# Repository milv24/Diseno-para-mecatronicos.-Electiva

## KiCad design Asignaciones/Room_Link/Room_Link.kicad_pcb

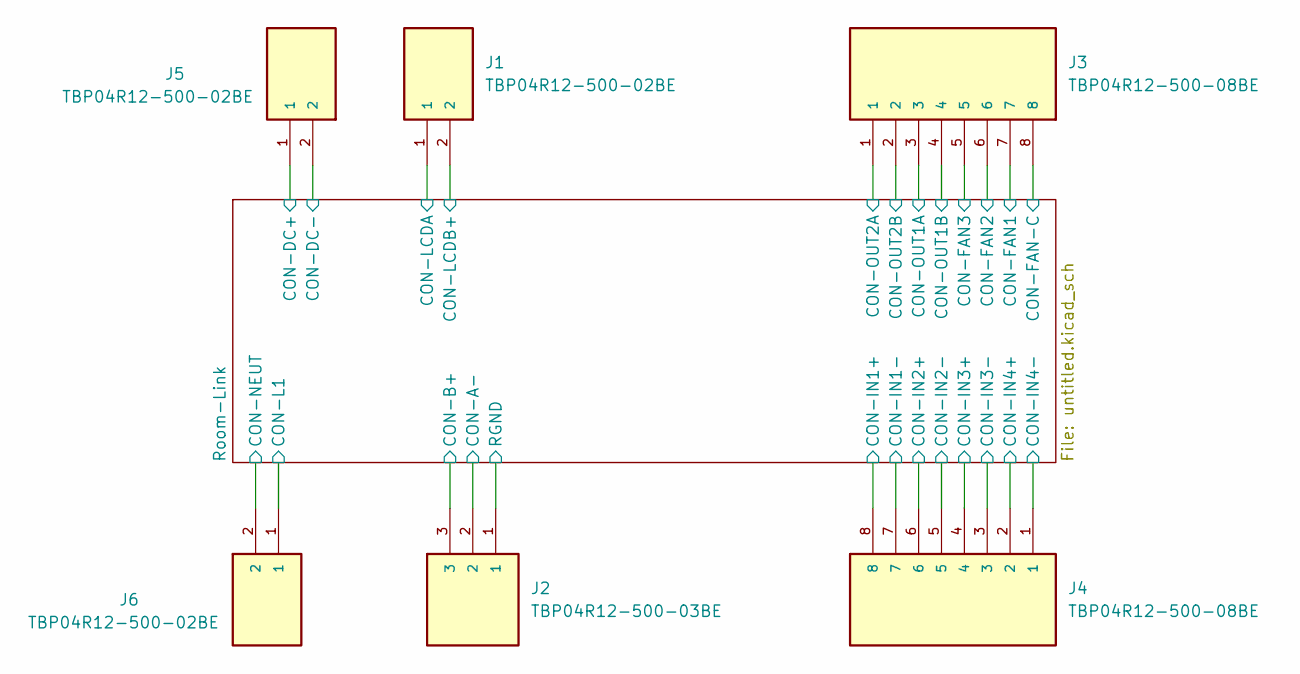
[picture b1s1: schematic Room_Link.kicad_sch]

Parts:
J1, J5, J6: TBP04R12-500-02BE; CUI_TBP04R12-500-02BE; PARTREV 1.0
J2: TBP04R12-500-03BE; CUI_TBP04R12-500-03BE; PARTREV 1.0
J3, J4: TBP04R12-500-08BE; CUI_TBP04R12-500-08BE; PARTREV 1.0

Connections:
/Room-Link/CON-A-: J2.2; also elsewhere on the board
/Room-Link/CON-DC+: J5.1
/Room-Link/CON-FAN1: J3.7; also elsewhere on the board
/Room-Link/CON-FAN2: J3.6; also elsewhere on the board
/Room-Link/CON-FAN3: J3.5; also elsewhere on the board
/Room-Link/CON-FAN-C: J3.8; also elsewhere on the board
/Room-Link/CON-IN1+: J4.8; also elsewhere on the board
/Room-Link/CON-IN1-: J4.7; also elsewhere on the board
/Room-Link/CON-IN2+: J4.6; also elsewhere on the board
/Room-Link/CON-IN2-: J4.5; also elsewhere on the board
/Room-Link/CON-IN3+: J4.4; also elsewhere on the board
/Room-Link/CON-IN3-: J4.3; also elsewhere on the board
/Room-Link/CON-IN4+: J4.2; also elsewhere on the board
/Room-Link/CON-IN4-: J4.1; also elsewhere on the board
/Room-Link/CON-L1: J6.1; also elsewhere on the board
/Room-Link/CON-LCDA: J1.1; also elsewhere on the board
/Room-Link/CON-LCDB+: J1.2; also elsewhere on the board
/Room-Link/CON-NEUT: J6.2; also elsewhere on the board
/Room-Link/CON-OUT1A: J3.3; also elsewhere on the board
/Room-Link/CON-OUT1B: J3.4; also elsewhere on the board
/Room-Link/CON-OUT2A: J3.2; also elsewhere on the board
/Room-Link/CON-OUT2B: J3.1; also elsewhere on the board
/Room-Link/RGND: J2.1; also elsewhere on the board

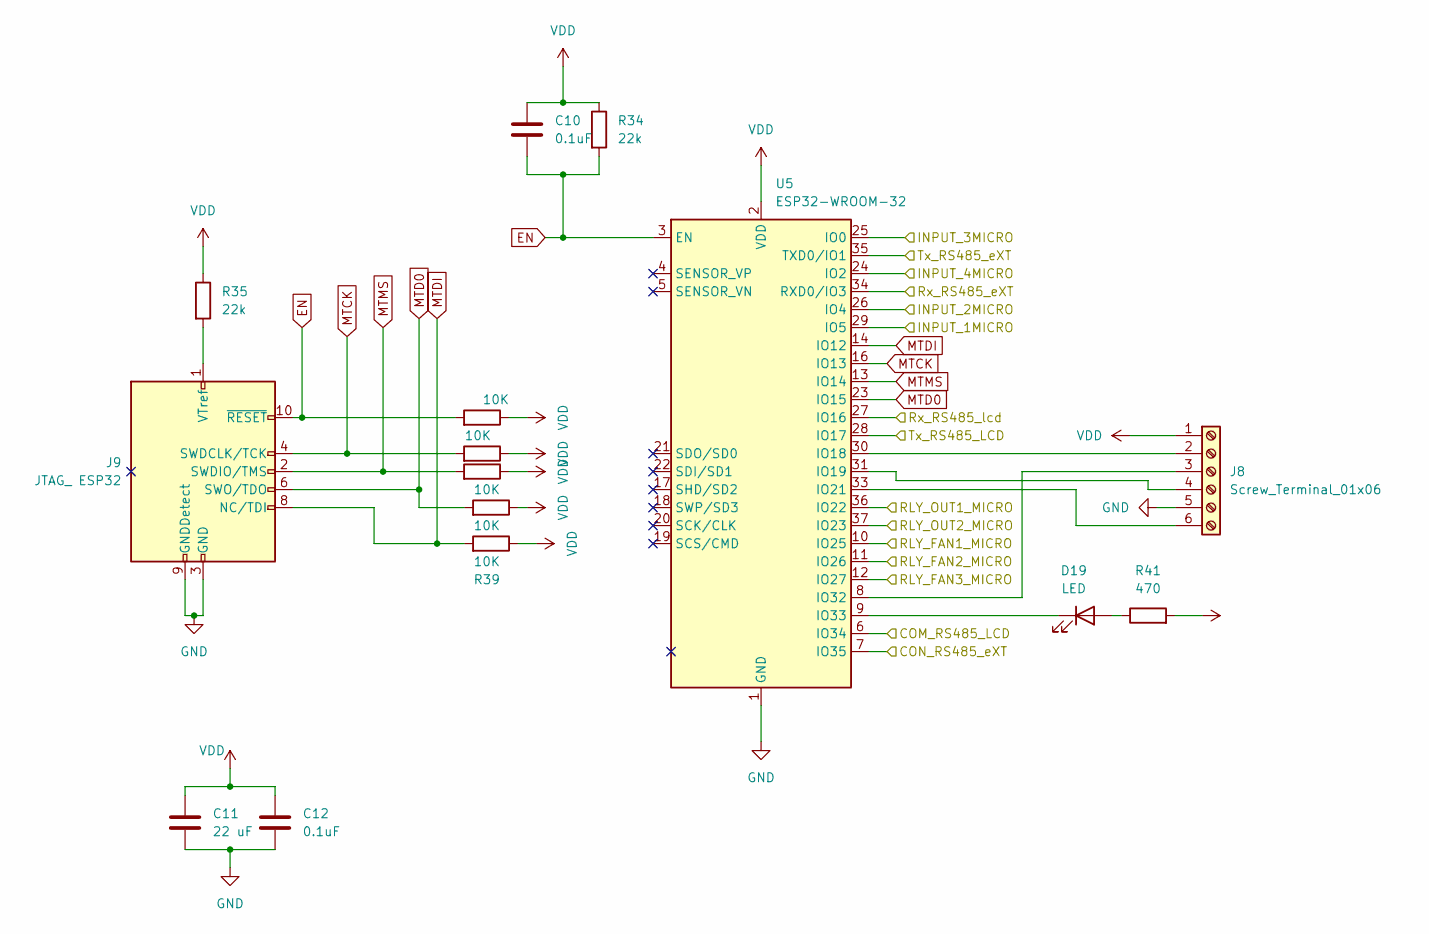
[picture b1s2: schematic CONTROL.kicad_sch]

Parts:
C10, C12: 0.1uF; C_0805_2012Metric
C11: 22 uF; C_0805_2012Metric
D19: LED; LED_0805_2012Metric
J8: Screw_Terminal_01x06; PinHeader_1x06_P2.54mm_Vertical_SMD_Pin1Left
J9: JTAG_ ESP32; PinHeader_2x05_P1.27mm_Vertical
R34, R35: 22k; R_0805_2012Metric
R36, R37, R38, R39, R40: 10K; R_0805_2012Metric
R41: 470; R_0805_2012Metric
U5: ESP32-WROOM-32

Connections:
/Room-Link/CONTROL/COM_RS485_LCD: U5.6 (IO34); also elsewhere on the board
/Room-Link/CONTROL/CON_RS485_eXT: U5.7 (IO35); also elsewhere on the board
/Room-Link/CONTROL/INPUT_1MICRO: U5.29 (IO5); also elsewhere on the board
/Room-Link/CONTROL/INPUT_2MICRO: U5.26 (IO4); also elsewhere on the board
/Room-Link/CONTROL/INPUT_3MICRO: U5.25 (IO0); also elsewhere on the board
/Room-Link/CONTROL/INPUT_4MICRO: U5.24 (IO2); also elsewhere on the board
/Room-Link/CONTROL/RLY_FAN1_MICRO: U5.10 (IO25); also elsewhere on the board
/Room-Link/CONTROL/RLY_FAN2_MICRO: U5.11 (IO26); also elsewhere on the board
/Room-Link/CONTROL/RLY_FAN3_MICRO: U5.12 (IO27); also elsewhere on the board
/Room-Link/CONTROL/RLY_OUT1_MICRO: U5.36 (IO22); also elsewhere on the board
/Room-Link/CONTROL/RLY_OUT2_MICRO: U5.37 (IO23); also elsewhere on the board
/Room-Link/CONTROL/Rx_RS485_eXT: U5.34 (RXD0/IO3); also elsewhere on the board
/Room-Link/CONTROL/Rx_RS485_lcd: U5.27 (IO16); also elsewhere on the board
/Room-Link/CONTROL/Tx_RS485_LCD: U5.28 (IO17); also elsewhere on the board
/Room-Link/CONTROL/Tx_RS485_eXT: U5.35 (TXD0/IO1); also elsewhere on the board
EN: C10.2, J9.10 (~RESET), R34.2, R40.2, U5.3 (EN)
MTCK: J9.4 (SWDCLK/TCK), R37.2, U5.16 (IO13)
MTD0: J9.6 (SWO/TDO), R38.2, U5.23 (IO15)
MTDI: J9.8 (NC/TDI), R39.2, U5.14 (IO12)
MTMS: J9.2 (SWDIO/TMS), R36.2, U5.13 (IO14)
unnamed: D19.2 (A), R41.1
unnamed: D19.1 (K), U5.9 (IO33)
unnamed: J8.2, U5.30 (IO18)
unnamed: J8.3, U5.8 (IO32)
unnamed: J8.4, U5.31 (IO19)
unnamed: J8.6, U5.33 (IO21)
unnamed: J9.1 (VTref), R35.2
VDD: C10.1, C11.1, C12.1, J8.1, R34.1, R35.1, R36.1, R37.1, R38.1, R39.1, R40.1, R41.2, U5.2 (VDD); also elsewhere on the board

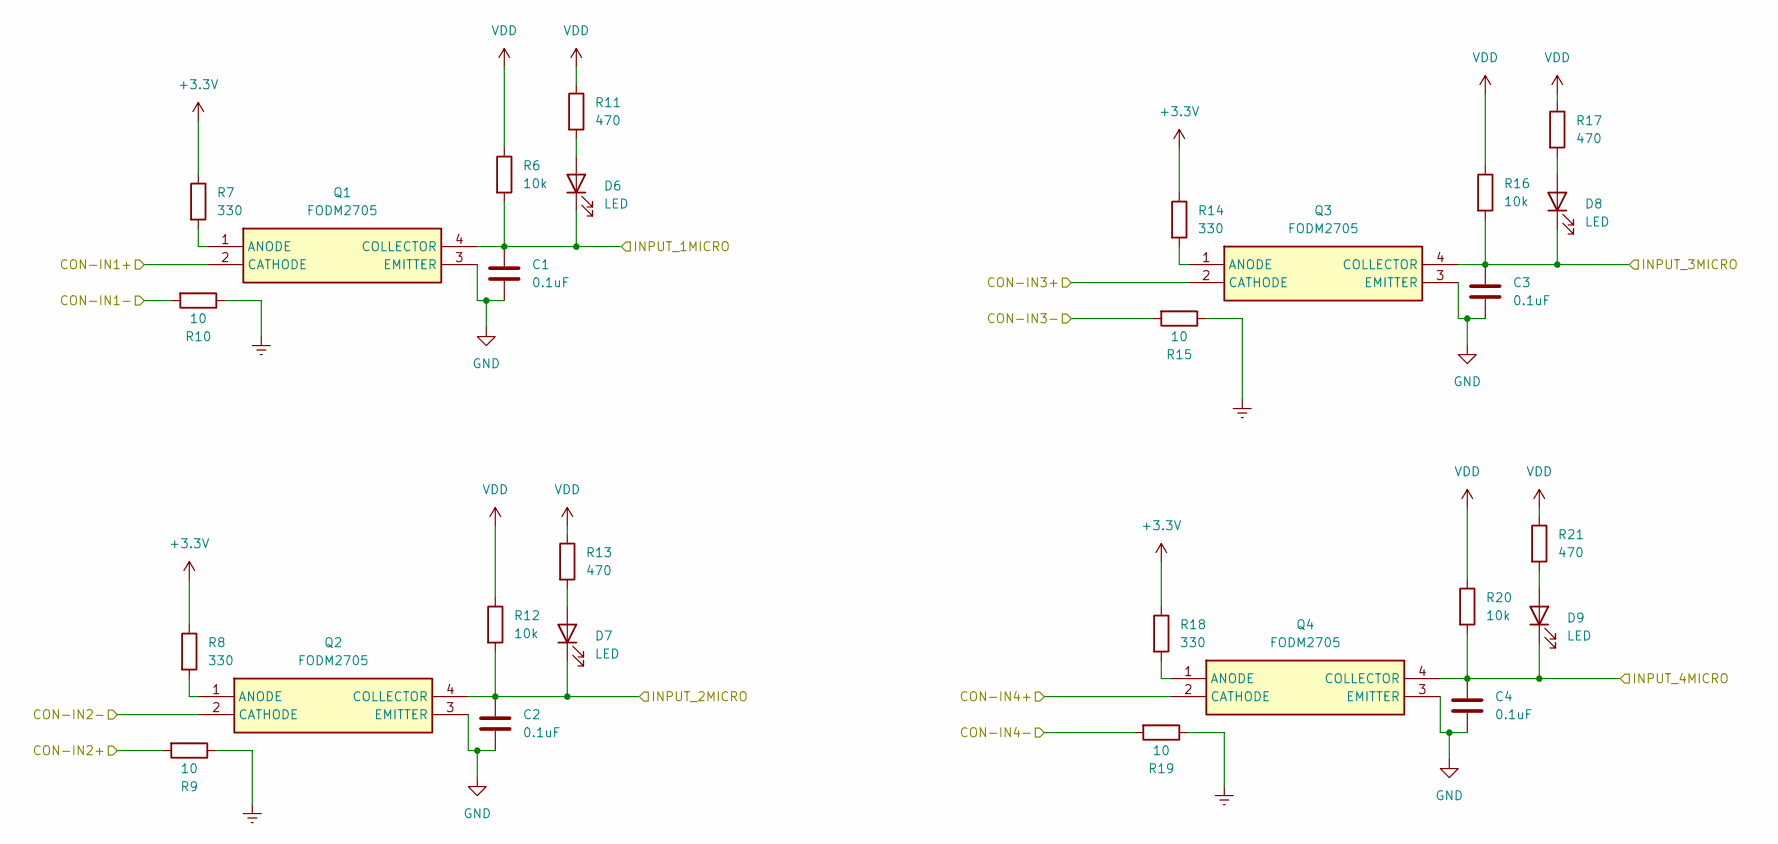
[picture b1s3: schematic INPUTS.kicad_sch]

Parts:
C1, C2, C3: 0.1uF; C_0805_2012Metric_Pad1.18x1.45mm_HandSolder
C4: 0.1uF; C_0805_2012Metric
D6, D7, D8, D9: LED; LED_0805_2012Metric
Q1, Q2, Q3, Q4: FODM2705; Manufacturer_Part_Number FODM2705; Mouser Part Number 512-FODM2705
R6, R12, R16, R20: 10k; R_0805_2012Metric
R7, R8, R14, R18: 330; R_0805_2012Metric
R9, R10, R15, R19: 10; R_0805_2012Metric
R11, R13, R17, R21: 470; R_0805_2012Metric

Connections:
+3.3V: R7.1, R8.1, R14.1, R18.1; also elsewhere on the board
/Room-Link/CON-IN1+: Q1.2 (CATHODE); also elsewhere on the board
/Room-Link/CON-IN1-: R10.2; also elsewhere on the board
/Room-Link/CON-IN2+: R9.2; also elsewhere on the board
/Room-Link/CON-IN2-: Q2.2 (CATHODE); also elsewhere on the board
/Room-Link/CON-IN3+: Q3.2 (CATHODE); also elsewhere on the board
/Room-Link/CON-IN3-: R15.2; also elsewhere on the board
/Room-Link/CON-IN4+: Q4.2 (CATHODE); also elsewhere on the board
/Room-Link/CON-IN4-: R19.2; also elsewhere on the board
/Room-Link/CONTROL/INPUT_1MICRO: C1.1, D6.1 (K), Q1.4 (COLLECTOR), R6.2; also elsewhere on the board
/Room-Link/CONTROL/INPUT_2MICRO: C2.1, D7.1 (K), Q2.4 (COLLECTOR), R12.2; also elsewhere on the board
/Room-Link/CONTROL/INPUT_3MICRO: C3.1, D8.1 (K), Q3.4 (COLLECTOR), R16.2; also elsewhere on the board
/Room-Link/CONTROL/INPUT_4MICRO: C4.1, D9.1 (K), Q4.4 (COLLECTOR), R20.2; also elsewhere on the board
Earth: R9.1, R10.1, R15.1, R19.1; also elsewhere on the board
unnamed: D6.2 (A), R11.2
unnamed: D7.2 (A), R13.2
unnamed: D8.2 (A), R17.2
unnamed: D9.2 (A), R21.2
unnamed: Q1.1 (ANODE), R7.2
unnamed: Q2.1 (ANODE), R8.2
unnamed: Q3.1 (ANODE), R14.2
unnamed: Q4.1 (ANODE), R18.2
VDD: R6.1, R11.1, R12.1, R13.1, R16.1, R17.1, R20.1, R21.1; also elsewhere on the board

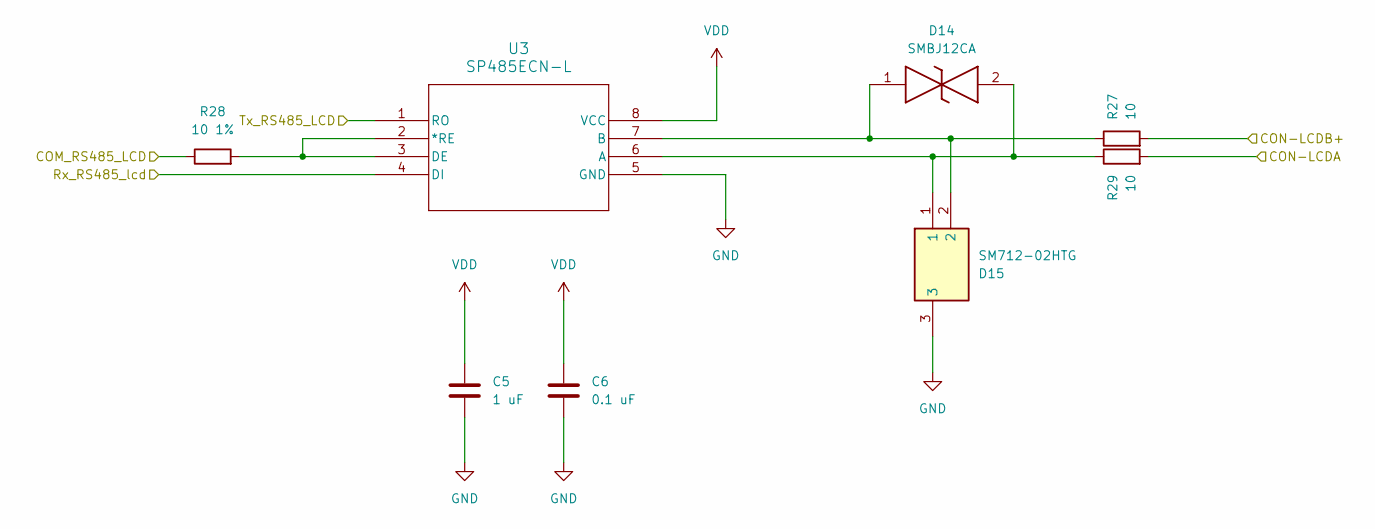
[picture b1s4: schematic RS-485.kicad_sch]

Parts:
C5: 1 uF; C_0805_2012Metric
C6: 0.1 uF; C_0805_2012Metric
D14: SMBJ12CA; Mouser Part Number 652-SMBJ12CA
D15: SM712-02HTG; SOT-23; Manufacturer_Part_Number SM712-02HTG; Mouser Part Number 576-SM712-02HTG
R27, R29: 10; R_0805_2012Metric
R28: 10 1%; R_0805_2012Metric
U3: SP485ECN-L; NSOIC-8-L

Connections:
/Room-Link/CON-LCDA: R29.2; also elsewhere on the board
/Room-Link/CON-LCDB+: R27.2; also elsewhere on the board
/Room-Link/CONTROL/COM_RS485_LCD: R28.1; also elsewhere on the board
/Room-Link/CONTROL/Rx_RS485_lcd: U3.4 (DI); also elsewhere on the board
/Room-Link/CONTROL/Tx_RS485_LCD: U3.1 (RO); also elsewhere on the board
unnamed: R28.2, U3.2 (*RE), U3.3 (DE)
unnamed: D14.2, D15.1, R29.1, U3.6 (A)
unnamed: D14.1, D15.2, R27.1, U3.7 (B)
VDD: C5.1, C6.1, U3.8 (VCC); also elsewhere on the board

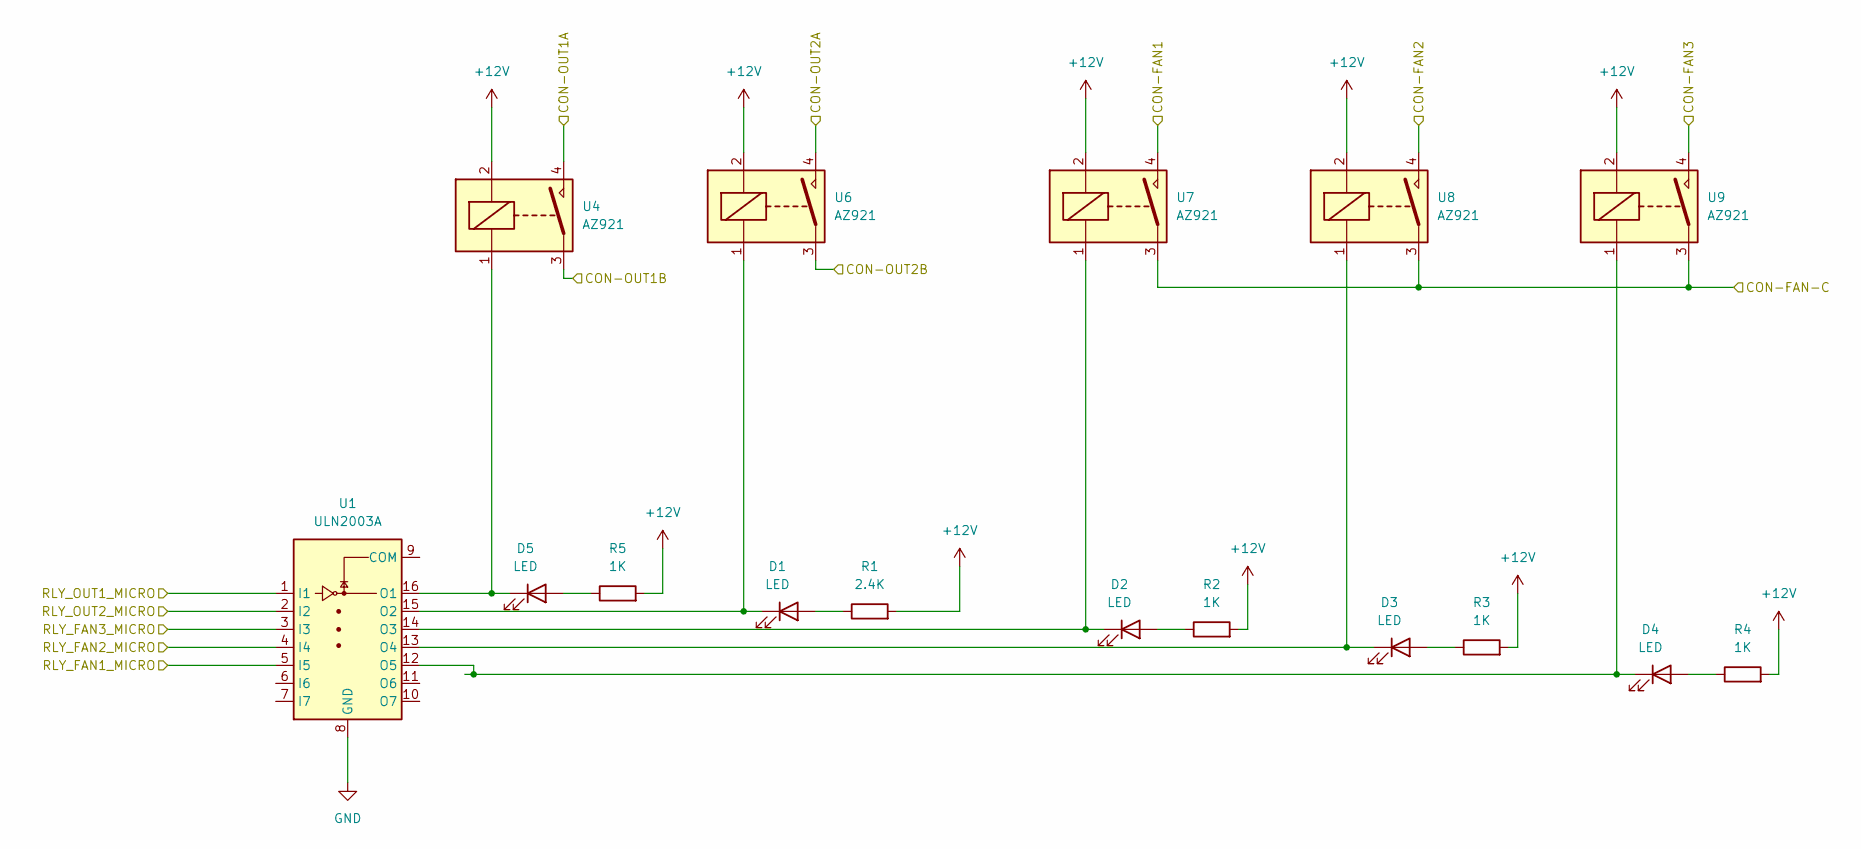
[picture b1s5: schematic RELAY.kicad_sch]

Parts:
D1, D2, D3, D4, D5: LED; LED_0805_2012Metric
R1: 2.4K; R_0805_2012Metric
R2, R3, R4, R5: 1K; R_0805_2012Metric
U1: ULN2003A; SOIC-16_3.9x9.9mm_P1.27mm
U4, U6, U7, U8, U9: AZ921

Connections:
/Room-Link/CON-FAN1: U7.4; also elsewhere on the board
/Room-Link/CON-FAN2: U8.4; also elsewhere on the board
/Room-Link/CON-FAN3: U9.4; also elsewhere on the board
/Room-Link/CON-FAN-C: U7.3, U8.3, U9.3; also elsewhere on the board
/Room-Link/CON-OUT1A: U4.4; also elsewhere on the board
/Room-Link/CON-OUT1B: U4.3; also elsewhere on the board
/Room-Link/CON-OUT2A: U6.4; also elsewhere on the board
/Room-Link/CON-OUT2B: U6.3; also elsewhere on the board
/Room-Link/CONTROL/RLY_FAN1_MICRO: U1.5 (I5); also elsewhere on the board
/Room-Link/CONTROL/RLY_FAN2_MICRO: U1.4 (I4); also elsewhere on the board
/Room-Link/CONTROL/RLY_FAN3_MICRO: U1.3 (I3); also elsewhere on the board
/Room-Link/CONTROL/RLY_OUT1_MICRO: U1.1 (I1); also elsewhere on the board
/Room-Link/CONTROL/RLY_OUT2_MICRO: U1.2 (I2); also elsewhere on the board
unnamed: D1.2 (A), R1.1
unnamed: D1.1 (K), U1.15 (O2), U6.1
unnamed: D2.2 (A), R2.1
unnamed: D2.1 (K), U1.14 (O3), U7.1
unnamed: D3.2 (A), R3.1
unnamed: D3.1 (K), U1.13 (O4), U8.1
unnamed: D4.2 (A), R4.1
unnamed: D4.1 (K), U1.12 (O5), U9.1
unnamed: D5.2 (A), R5.1
unnamed: D5.1 (K), U1.16 (O1), U4.1

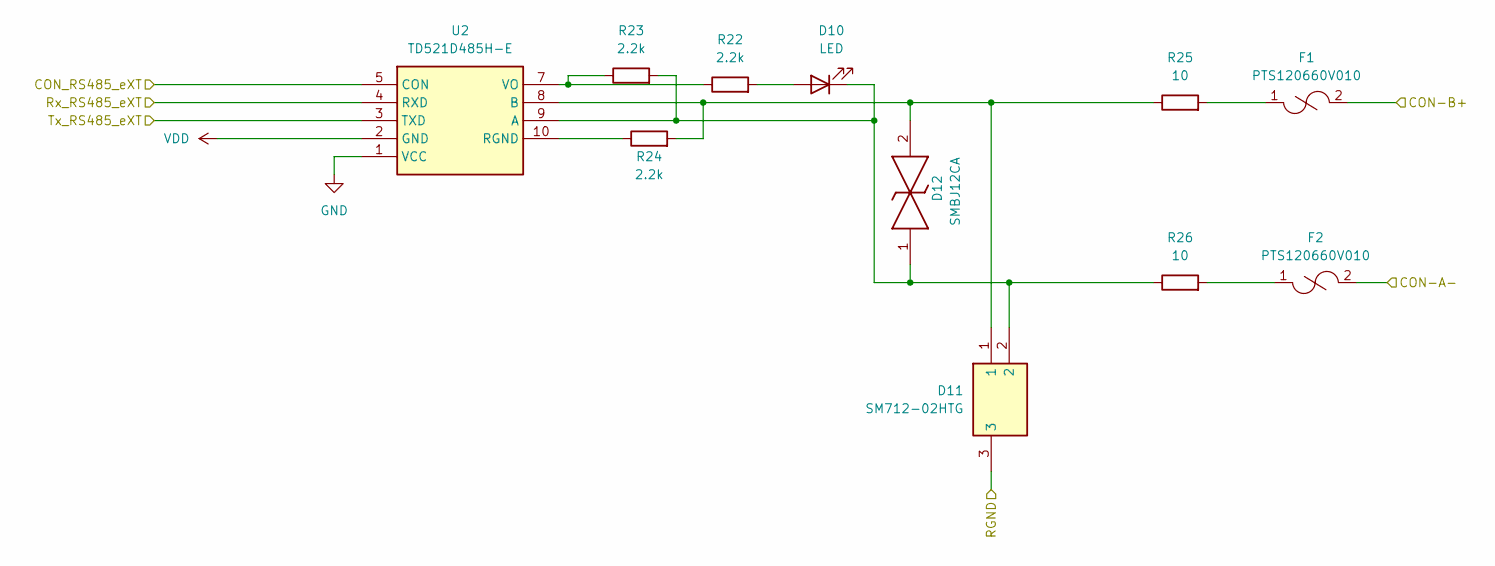
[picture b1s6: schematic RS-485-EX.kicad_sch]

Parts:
D10: LED; LED_0805_2012Metric
D11: SM712-02HTG; SOT-23; Manufacturer_Part_Number SM712-02HTG; Mouser Part Number 576-SM712-02HTG
D12: SMBJ12CA; Mouser Part Number 652-SMBJ12CA
F1, F2: PTS120660V010; FUSC3216X68N
R22, R23, R24: 2.2k; R_0805_2012Metric
R25, R26: 10; R_0805_2012Metric
U2: TD521D485H-E; Manufacturer_Part_Number TD521D485

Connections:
/Room-Link/CON-A-: F2.2; also elsewhere on the board
/Room-Link/CONTROL/CON_RS485_eXT: U2.5 (CON); also elsewhere on the board
/Room-Link/CONTROL/Rx_RS485_eXT: U2.4 (RXD); also elsewhere on the board
/Room-Link/CONTROL/Tx_RS485_eXT: U2.3 (TXD); also elsewhere on the board
/Room-Link/RGND: D11.3; also elsewhere on the board
unnamed: D10.2 (A), R22.2
unnamed: D10.1 (K), D11.2, D12.1, R23.2, R26.1, U2.9 (A)
unnamed: F1.1, R25.2
unnamed: F2.1, R26.2
unnamed: D11.1, D12.2, R24.2, R25.1, U2.8 (B)
unnamed: R24.1, U2.10 (RGND)
unnamed: R22.1, R23.1, U2.7 (VO)
VDD: U2.2 (GND); also elsewhere on the board

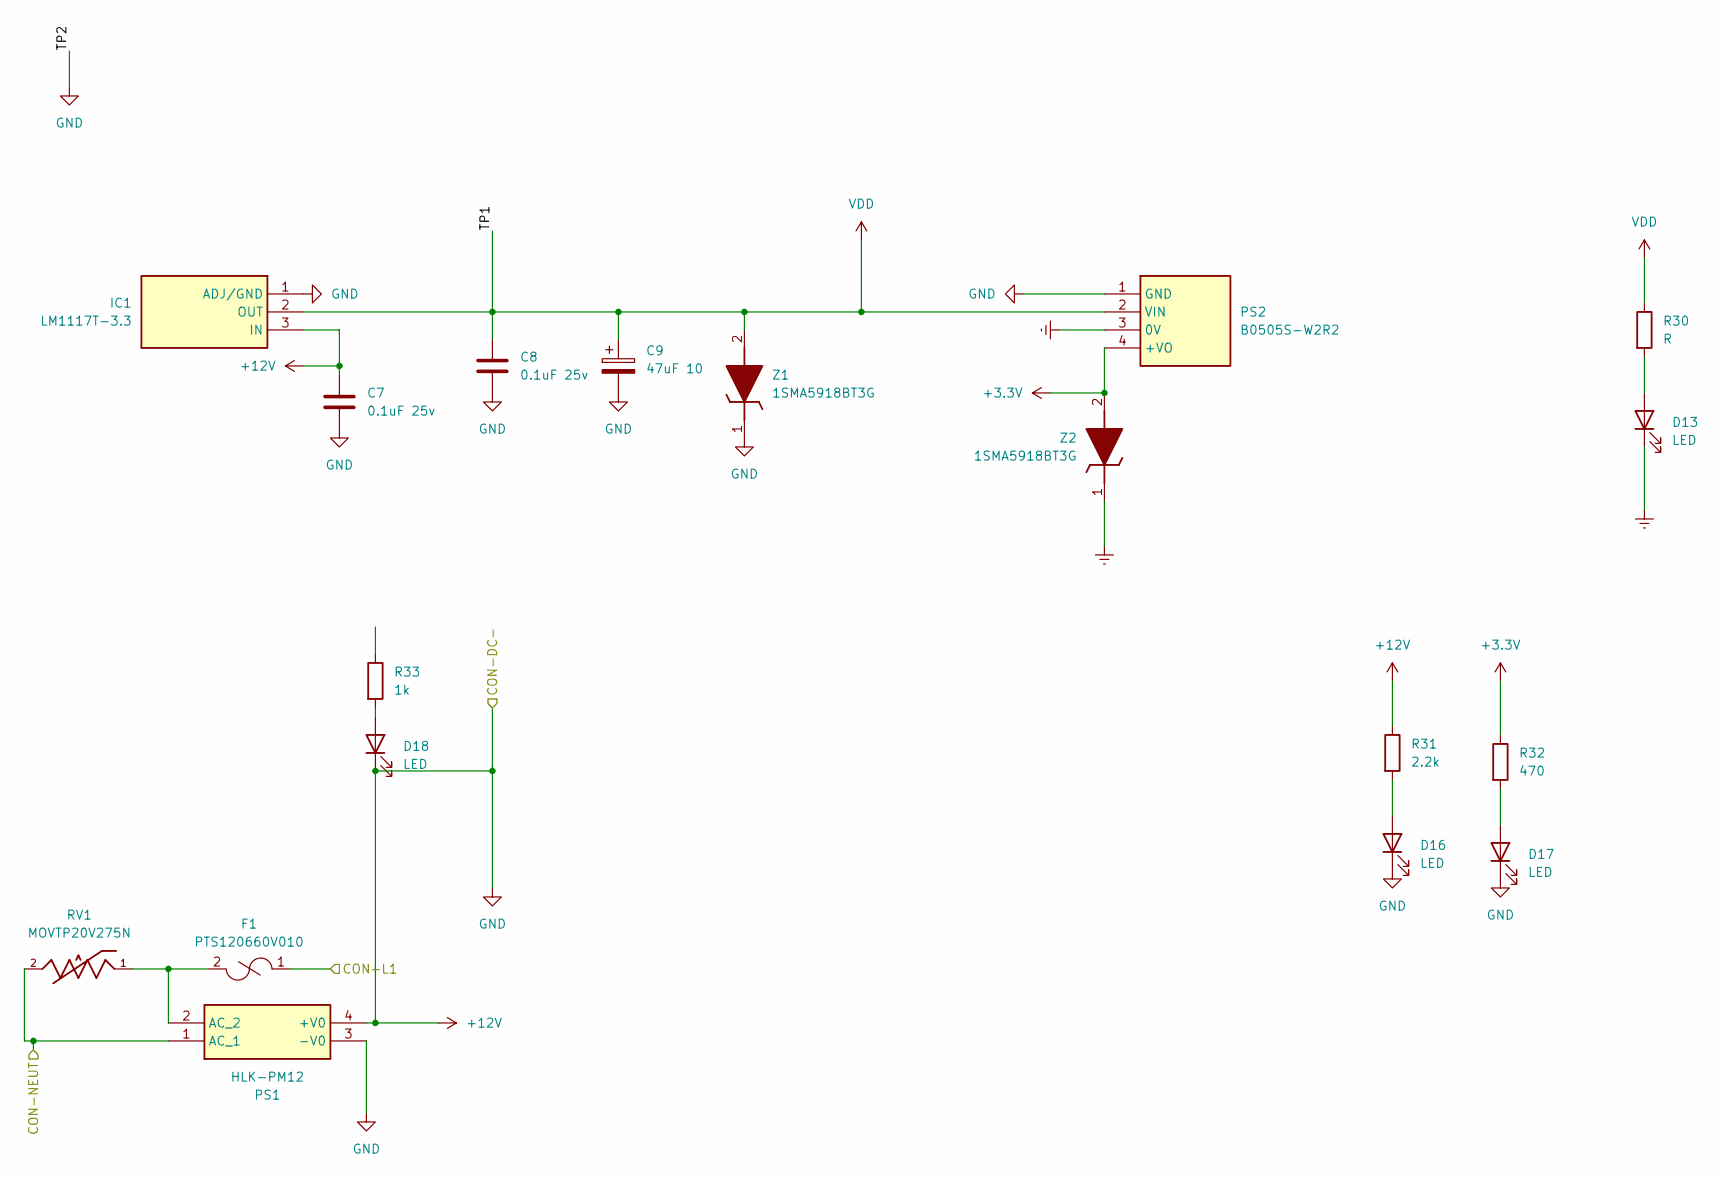
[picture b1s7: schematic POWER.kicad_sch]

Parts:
C7, C8: 0.1uF 25v; C_0805_2012Metric
C9: 47uF 10; C_0805_2012Metric
D13, D16, D17, D18: LED; LED_0805_2012Metric
F1: PTS120660V010; Fuseholder_Cylinder-5x20mm_Stelvio-Kontek_PTF78_Horizontal_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
IC1: LM1117T-3.3; TO254P470X1016X2222-3P; Manufacturer_Part_Number LM1117T-3.3; Mouser Part Number 926-LM1117T-33
PS1: HLK-PM12; HLKPM12; Manufacturer_Part_Number HLK-PM12
PS2: B0505S-W2R2; B0505SW2R2; Manufacturer_Part_Number B0505S-W2R2
R30: R; R_0805_2012Metric
R31: 2.2k; R_0805_2012Metric
R32: 470; R_0805_2012Metric
R33: 1k; R_0805_2012Metric
RV1: MOVTP20V275N; B72210S1140K501; Manufacturer_Part_Number MOVTP20V275N
Z1, Z2: 1SMA5918BT3G; D_SMB; Manufacturer_Part_Number 1SMA5918BT3G; Mouser Part Number 863-1SMA5918BT3G

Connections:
+3.3V: PS2.4 (+VO), R32.1, Z2.2 (A); also elsewhere on the board
/Room-Link/CON-NEUT: PS1.1 (AC_1), RV1.2; also elsewhere on the board
Earth: D13.1 (K), PS2.3 (0V), Z2.1 (K); also elsewhere on the board
unnamed: D13.2 (A), R30.2
unnamed: D16.2 (A), R31.2
unnamed: D17.2 (A), R32.2
unnamed: D18.2 (A), R33.2
unnamed 67: F1.1; also elsewhere on the board
VDD: C8.1, C9.1, IC1.2 (OUT), PS2.2 (VIN), R30.1, Z1.2 (A); also elsewhere on the board

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
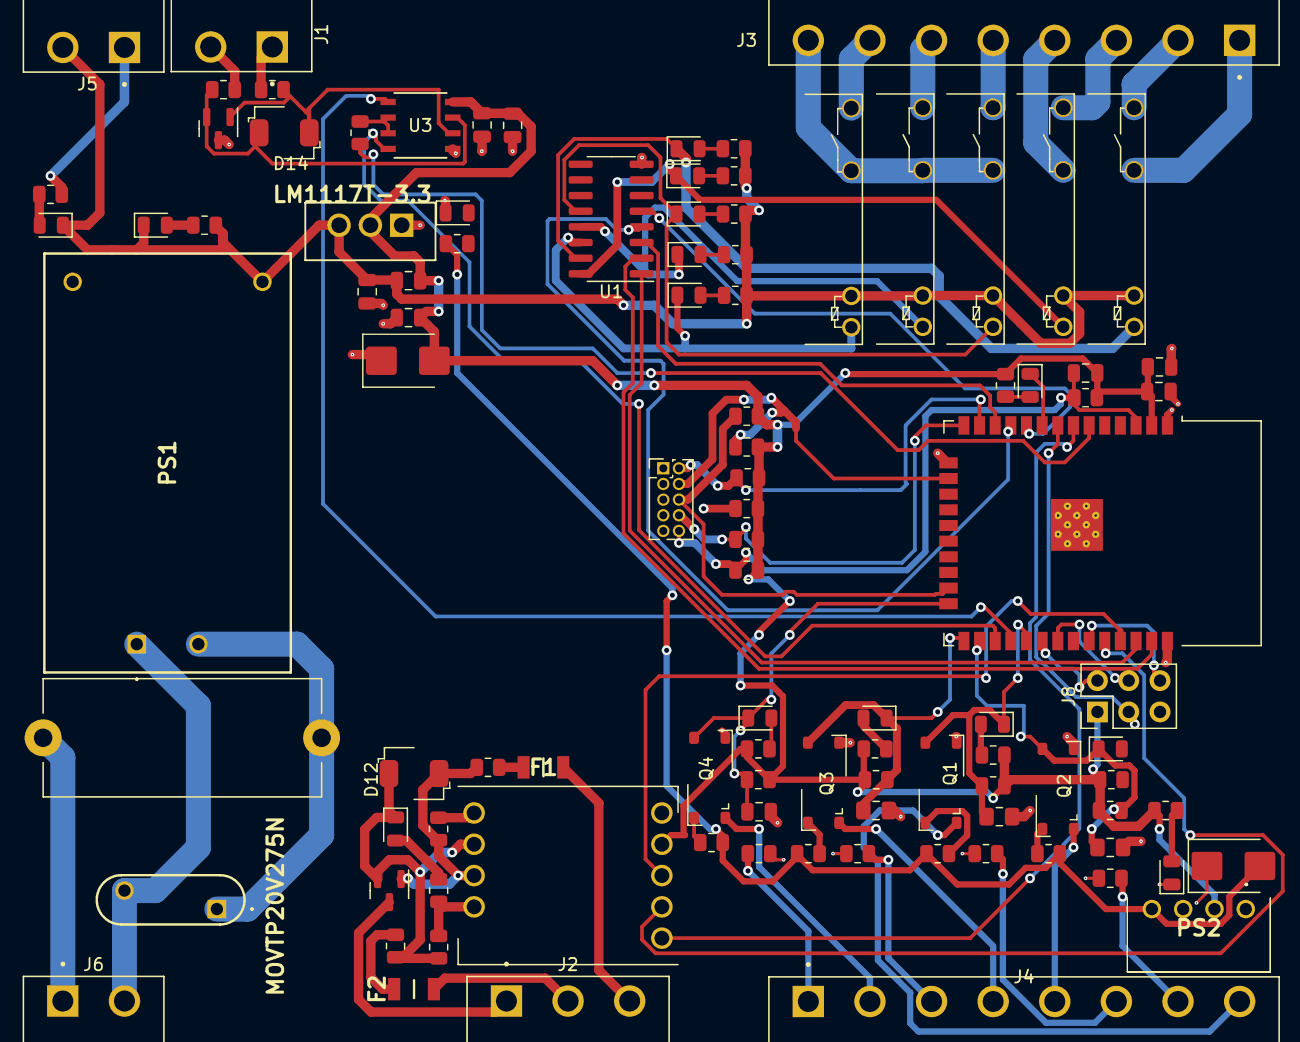
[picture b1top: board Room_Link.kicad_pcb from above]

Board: 4 copper layers, 102 parts (0 on the bottom side), 88 nets.

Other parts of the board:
F3: PTS120660V010; Fuseholder_Cylinder-5x20mm_Stelvio-Kontek_PTF78_Horizontal_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

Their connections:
/Room-Link/CON-L1: F3.1; also elsewhere on the board

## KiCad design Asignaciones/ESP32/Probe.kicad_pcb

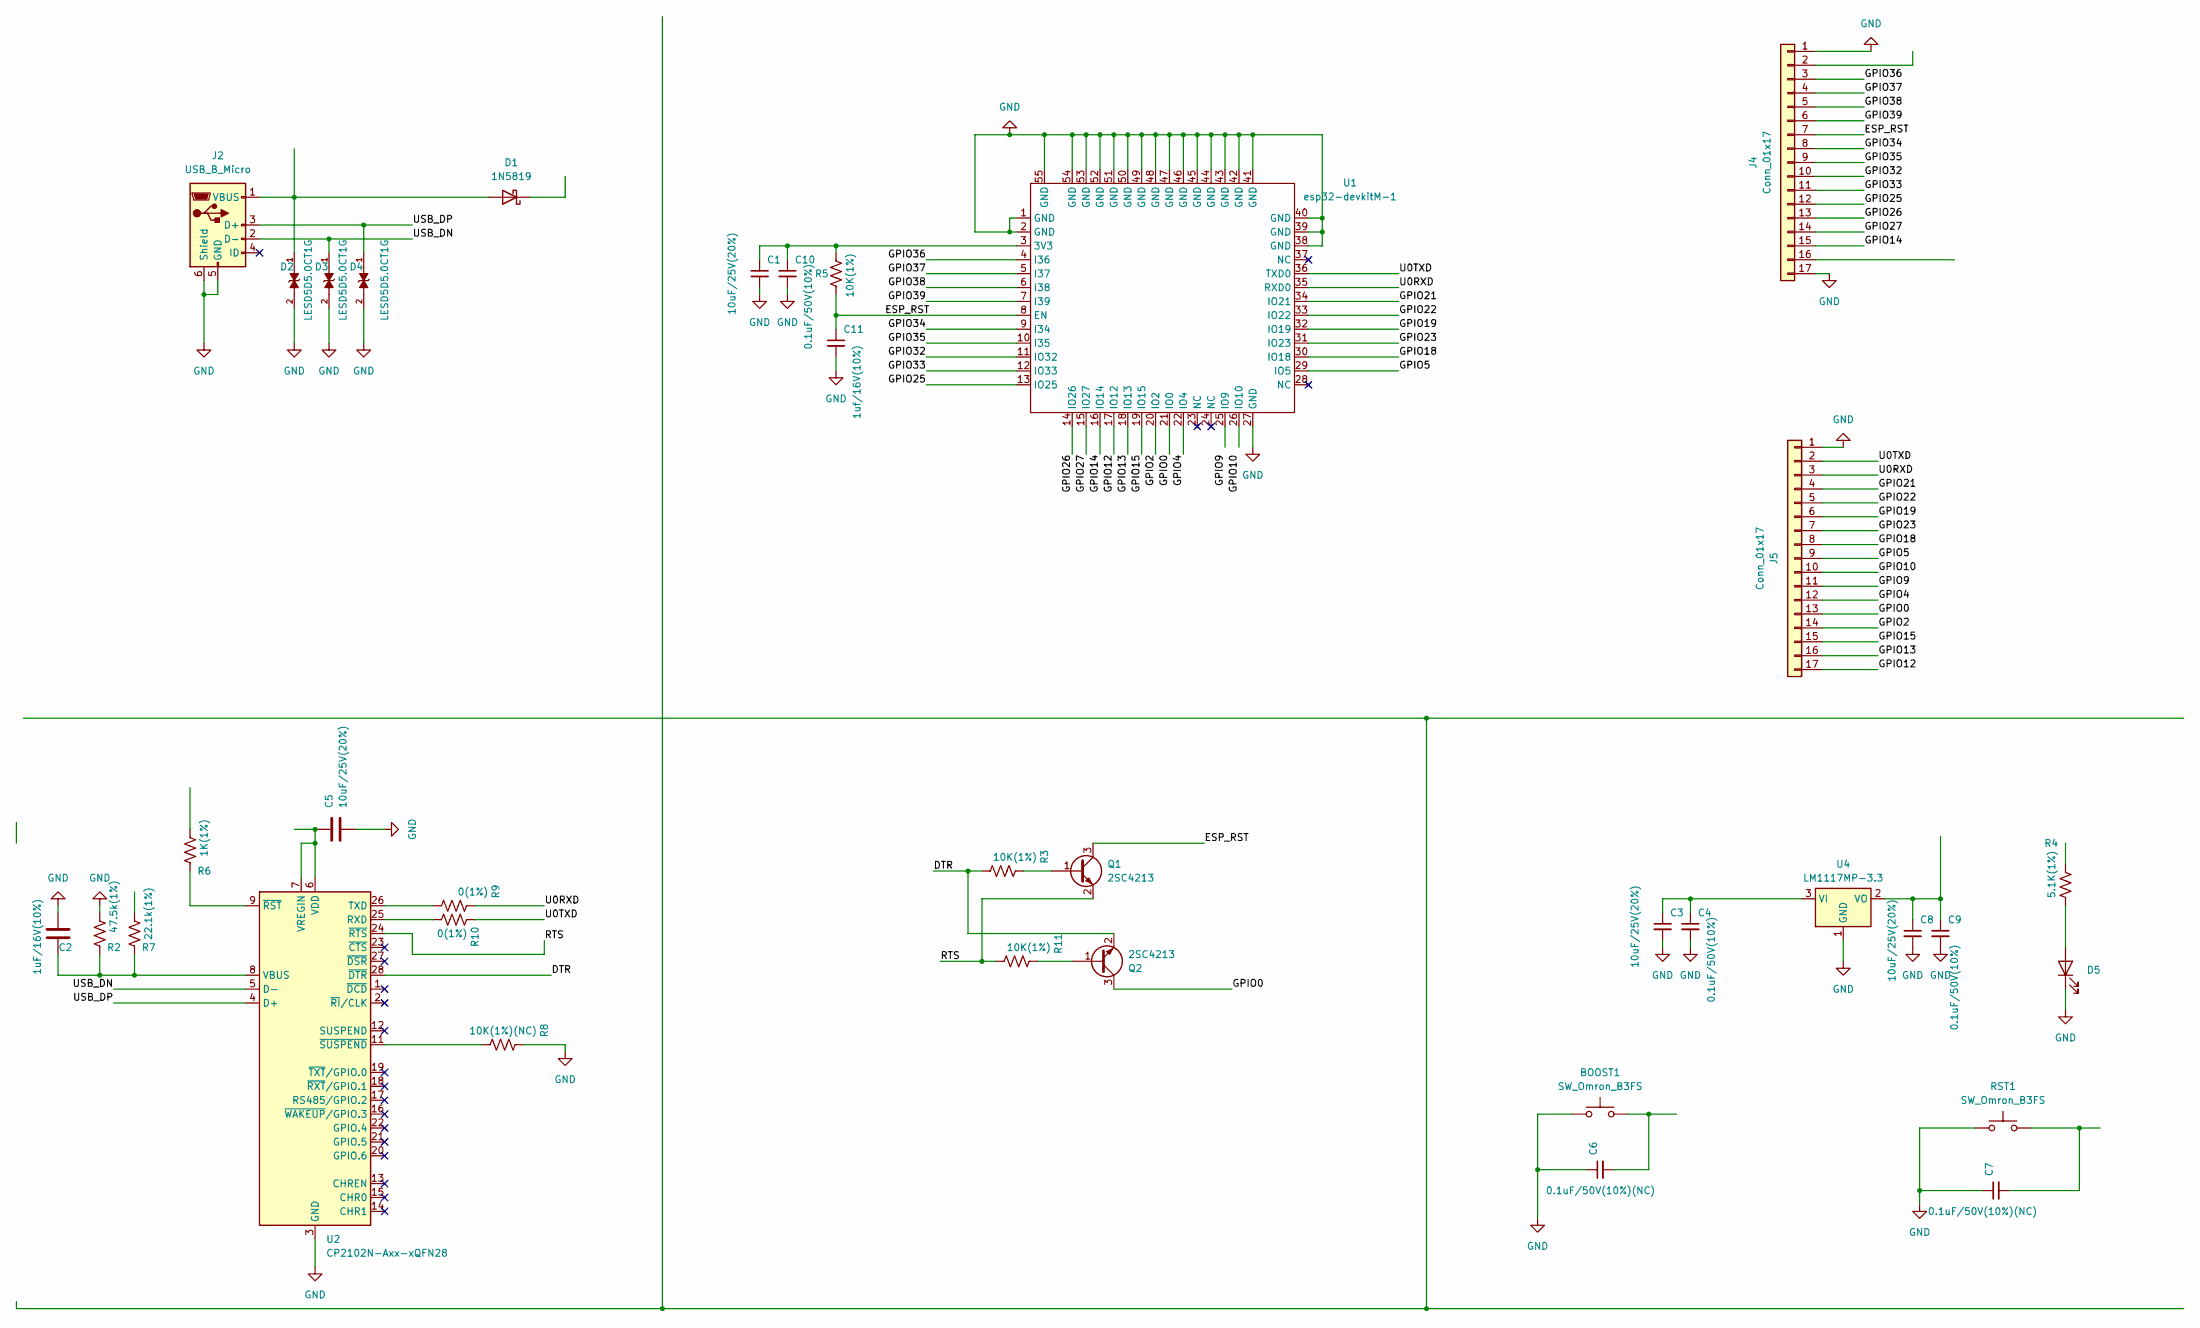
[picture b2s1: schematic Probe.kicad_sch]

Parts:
BOOST1: SW_Omron_B3FS; SW_SPST_PTS810
C1, C3, C5, C8: 10uF/25V(20%); C_0805_2012Metric_Pad1.18x1.45mm_HandSolder
C2: 1uF/16V(10%); C_0805_2012Metric_Pad1.18x1.45mm_HandSolder
C4, C9, C10: 0.1uF/50V(10%); C_0805_2012Metric_Pad1.18x1.45mm_HandSolder
C6, C7: 0.1uF/50V(10%)(NC); C_0805_2012Metric_Pad1.18x1.45mm_HandSolder
C11: 1uf/16V(10%); C_0805_2012Metric_Pad1.18x1.45mm_HandSolder
D1: 1N5819; D_0805_2012Metric_Pad1.15x1.40mm_HandSolder
D2, D3, D4: LESD5D5.0CT1G; TVS_LESD5D5.0CT1G; PARTREV O
D5: LED; LED_0805_2012Metric
J2: USB_B_Micro; USB_Micro-B_Wuerth_629105150521
J4, J5: Conn_01x17; PinHeader_1x17_P2.54mm_Vertical
Q1, Q2: 2SC4213; SOT-323_SC-70_Handsoldering
R2: 47.5k(1%); R_0603_1608Metric_Pad0.98x0.95mm_HandSolder
R3, R5, R11: 10K(1%); R_0603_1608Metric_Pad0.98x0.95mm_HandSolder
R4: 5.1K(1%); R_0603_1608Metric_Pad0.98x0.95mm_HandSolder
R6: 1K(1%); R_0603_1608Metric_Pad0.98x0.95mm_HandSolder
R7: 22.1k(1%); R_0603_1608Metric_Pad0.98x0.95mm_HandSolder
R8: 10K(1%)(NC); R_0603_1608Metric_Pad0.98x0.95mm_HandSolder
R9, R10: 0(1%); R_0603_1608Metric_Pad0.98x0.95mm_HandSolder
RST1: SW_Omron_B3FS; SW_SPST_PTS810
U1: esp32-devkitM-1; MODULE_ESP32-MINI-1U-N4
U2: CP2102N-Axx-xQFN28; QFN-28-1EP_5x5mm_P0.5mm_EP3.35x3.35mm
U4: LM1117MP-3.3; SOT-223-3_TabPin2

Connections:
/DTR: Q2.2 (E), R3.2, U2.28 (~DTR)
/ESP_RST: C11.1, J4.7, Q1.3 (C), R5.2, U1.8 (EN)
/GPIO0: J5.13, Q2.3 (C), U1.21 (IO0)
/GPIO2: J5.14, U1.20 (IO2)
/GPIO4: J5.12, U1.22 (IO4)
/GPIO5: J5.9, U1.29 (IO5)
/GPIO9: J5.11
/GPIO10: J5.10
/GPIO12: J5.17, U1.17 (IO12)
/GPIO13: J5.16, U1.18 (IO13)
/GPIO14: J4.15, U1.16 (IO14)
/GPIO15: J5.15, U1.19 (IO15)
/GPIO18: J5.8, U1.30 (IO18)
/GPIO19: J5.6, U1.32 (IO19)
/GPIO21: J5.4, U1.34 (IO21)
/GPIO22: J5.5, U1.33 (IO22)
/GPIO23: J5.7, U1.31 (IO23)
/GPIO25: J4.12, U1.13 (IO25)
/GPIO26: J4.13, U1.14 (IO26)
/GPIO27: J4.14, U1.15 (IO27)
/GPIO32: J4.10, U1.11 (IO32)
/GPIO33: J4.11, U1.12 (IO33)
/GPIO34: J4.8, U1.9 (I34)
/GPIO35: J4.9, U1.10 (I35)
/GPIO36: J4.3, U1.4 (I36)
/GPIO37: J4.4, U1.5 (I37)
/GPIO38: J4.5, U1.6 (I38)
/GPIO39: J4.6, U1.7 (I39)
/RTS: Q1.2 (E), R11.2, U2.24 (~RTS)
/U0RXD: J5.3, R9.1, U1.35 (RXD0)
/U0TXD: J5.2, R10.1, U1.36 (TXD0)
/USB_DN: D3.1, J2.2 (D-), U2.5 (D-)
/USB_DP: D4.1, J2.3 (D+), U2.4 (D+)
GND: BOOST1.1, C1.2, C2.1, C3.2, C4.2, C5.2, C6.1, C7.1, C8.2, C9.2, C10.2, C11.2, D2.2, D3.2, D4.2, D5.1 (K), J2.5 (GND), J2.6 (Shield), J4.1, J4.17, J5.1, R2.1, R8.1, RST1.1, U1.1 (GND), U1.2 (GND), U1.27 (GND), U1.38 (GND), U1.39 (GND), U1.40 (GND), U1.41 (GND), U1.42 (GND), U1.43 (GND), U1.44 (GND), U1.45 (GND), U1.46 (GND), U1.47 (GND), U1.48 (GND), U1.49 (GND), U1.50 (GND), U1.51 (GND), U1.52 (GND), U1.53 (GND), U1.54 (GND), U1.55 (GND), U2.3 (GND), U2.29 (GND), U4.1 (GND)
unnamed: BOOST1.2, C6.2
unnamed: C7.2, RST1.2
unnamed: D1.2 (A), D2.1, J2.1 (VBUS)
unnamed: D5.2 (A), R4.2
unnamed: Q1.1 (B), R3.1
unnamed: Q2.1 (B), R11.1
unnamed: C1.1, C10.1, R5.1, U1.3 (3V3)
unnamed: R10.2, U2.25 (RXD)
unnamed: R9.2, U2.26 (TXD)
unnamed: C2.2, R2.2, R7.2, U2.8 (VBUS)
unnamed: C5.1, U2.6 (VDD), U2.7 (VREGIN)
unnamed: R6.1, U2.9 (~RST)
unnamed: R8.2, U2.11 (~SUSPEND)
unnamed: C3.1, C4.1, U4.3 (VI)
unnamed: C8.1, C9.1, U4.2 (VO)

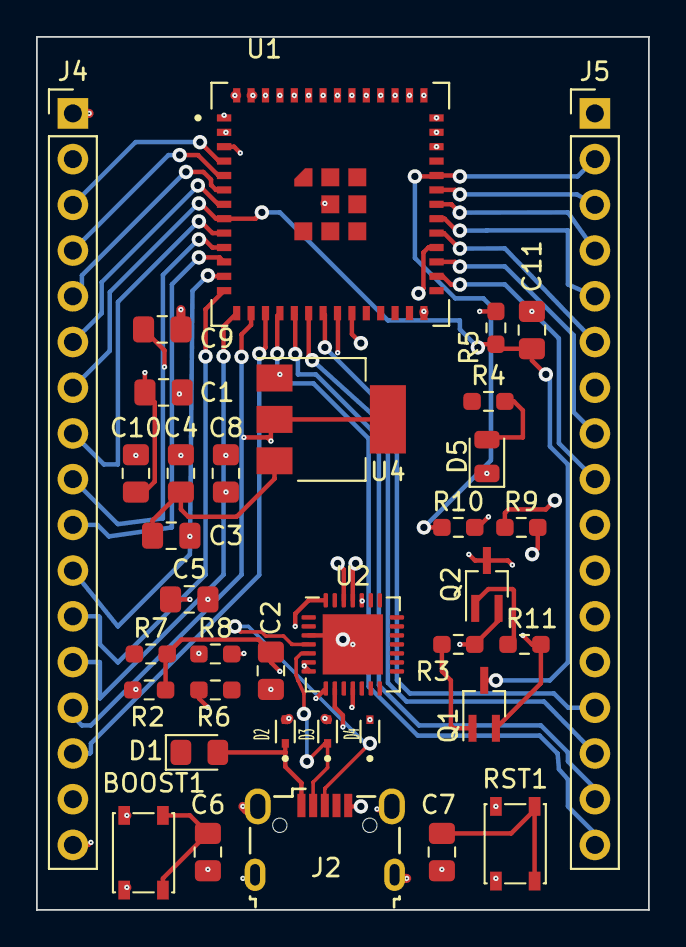
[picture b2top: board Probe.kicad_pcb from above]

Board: 4 copper layers, 34.0 x 48.5 mm, 36 parts (0 on the bottom side), 47 nets.

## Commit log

2023-05-19 Repositorio para Electiva
2023-05-19 primeros 2 capitulos y resumen git subidos
2023-06-01 Plantilla Especificacion Added
2023-06-02 Diseno de ESP32 para clase
2023-06-17 Nuevas asignaciones y cambios
2023-06-24 Nuevos cambios del Room-Link
2023-07-16 ROOM-LINK update KICAD
2023-07-16 Added new changes ROOM-LINK
2023-07-29 Added nuevos cambios
2023-07-29 new changes added
2023-08-04 Place component Added & routing
2023-08-04 Terminado'disque'
